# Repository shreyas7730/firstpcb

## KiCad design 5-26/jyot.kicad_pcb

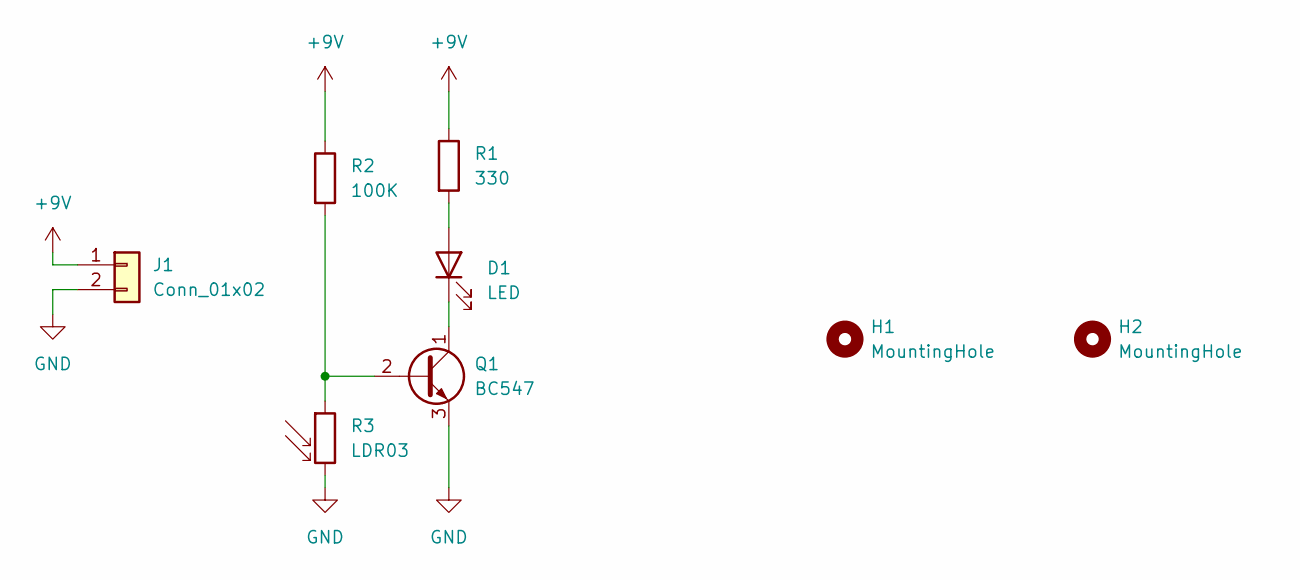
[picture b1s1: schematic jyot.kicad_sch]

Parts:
D1: LED; LED_D3.0mm_Horizontal_O6.35mm_Z10.0mm
H1, H2: MountingHole; MountingHole_3.2mm_M3
J1: Conn_01x02; PinHeader_1x02_P2.54mm_Vertical
Q1: BC547; TO-92_Inline
R1: 330; R_Axial_DIN0204_L3.6mm_D1.6mm_P5.08mm_Horizontal
R2: 100K; R_Axial_DIN0204_L3.6mm_D1.6mm_P5.08mm_Horizontal
R3: LDR03; R_LDR_10x8.5mm_P7.6mm_Vertical

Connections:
+9V: J1.1, R1.1, R2.1
GND: J1.2, Q1.3 (E), R3.2
unnamed: D1.2 (A), R1.2
unnamed: D1.1 (K), Q1.1 (C)
unnamed: Q1.2 (B), R2.2, R3.1

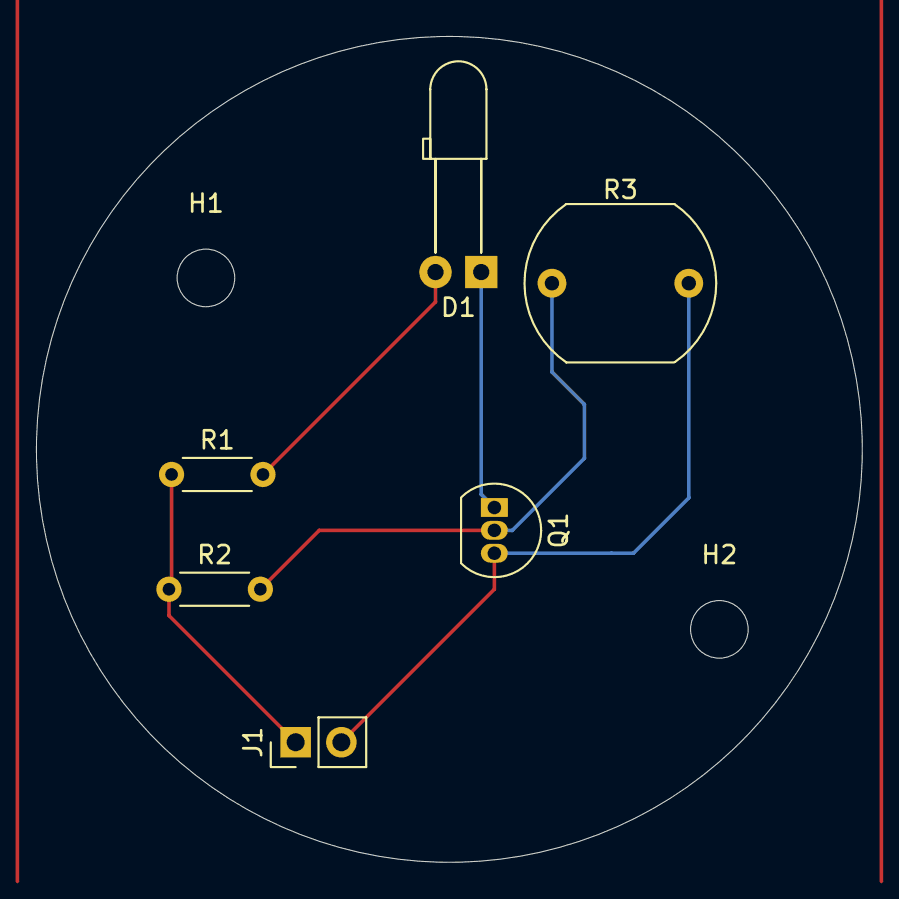
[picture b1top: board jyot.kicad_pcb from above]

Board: 2 copper layers, 45.9 x 45.9 mm, 8 parts (0 on the bottom side), 5 nets.
